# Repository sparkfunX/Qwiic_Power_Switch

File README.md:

# Qwiic Power Switch

A power switch for your Qwiic system.

[Qwiic Power Switch (SPX-16740)](https://www.sparkfun.com/products/16740)

The Qwiic Power Switch is a simple little board which can be used to switch the power to your Qwiic
system. Many Qwiic boards draw very little current when not being used, but there are some that draw
significantly more. The power switch allows you to switch the power to those boards, so you can minimize the
current draw and extend your battery life when you need to.

When the Qwiic Power Switch is turned off, the I2C wires are isolated too which prevents the pull-up
resistors from feeding parasitic power to your Qwiic boards. The power switch can also be used to
isolate a 400kHz bus from a 100kHz bus; the slower bus can be disconnected during fast-mode communication
without disabling the power.

The heart of the Qwiic Power Switch is the TI PCA9536 4-Bit I2C I/O Expander. We have broken out GPIO pins
1 and 2 so you can use them as general purpose inputs or outputs.

## Repository Contents

- **/Documents** - Datasheets etc.
- **/Hardware** - Eagle design files
- **LICENSE.md** contains the licence information

## Library

- **[Arduino Library](https://github.com/sparkfun/SparkFun_Qwiic_Power_Switch_Arduino_Library)** - Library for the power switch

## License Information

This product is _**open source**_!

Please review the LICENSE.md file for license information.

If you have any questions or concerns on licensing, please contact technical support on our [SparkFun forums](https://forum.sparkfun.com/viewforum.php?f=123).

Distributed as-is; no warranty is given.

- Your friends at SparkFun.

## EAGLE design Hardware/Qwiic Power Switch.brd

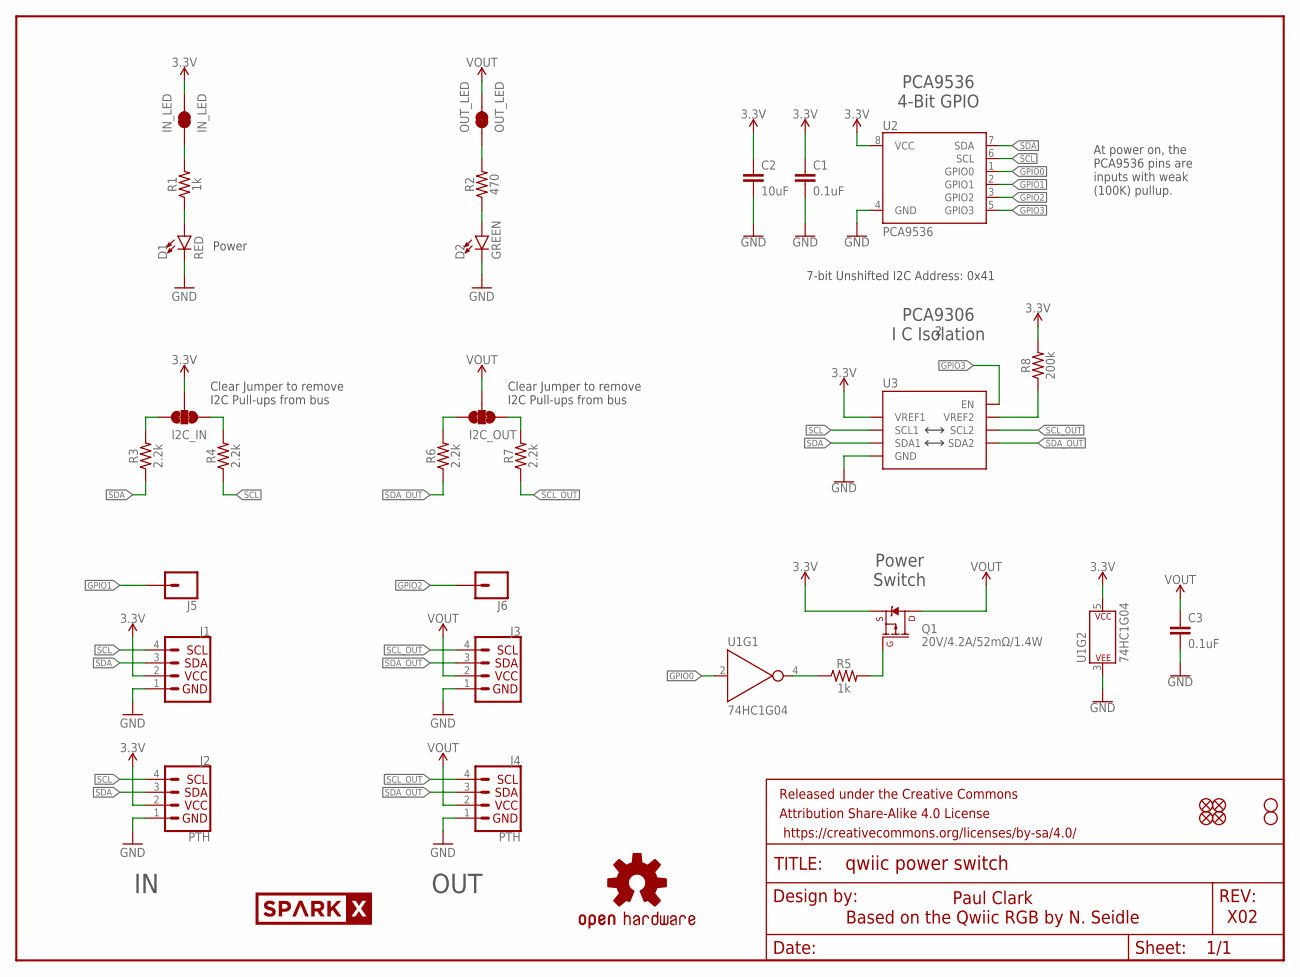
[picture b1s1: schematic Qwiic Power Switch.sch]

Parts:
C1, C3: 0.1uF; 0603
C2: 10uF; 0603
D1: RED; LED-0603
D2: GREEN; LED-0603
FRAME1: FRAME-LETTER; CREATIVE_COMMONS
I2C_IN, I2C_OUT: JUMPER-SMT_3_2-NC_TRACE_SILK; SMT-JUMPER_3_2-NC_TRACE_SILK
IN_LED: IN_LED; SMT-JUMPER_2_NC_TRACE_SILK
J1, J3: Qwiic Right Angle; JST04_1MM_RA
J2, J4: PTH; 1X04_NO_SILK
J5, J6: CONN_01PTH_NO_SILK_YES_STOP; 1X01_NO_SILK
JP1, JP2, JP5, JP6: FIDUCIAL1X2; FIDUCIAL-1X2
JP3, JP4: STAND-OFF
LOGO1: OSHW-LOGOMINI; OSHW-LOGO-MINI
OUT_LED: OUT_LED; SMT-JUMPER_2_NC_TRACE_SILK
Q1: 20V/4.2A/52mΩ/1.4W; SOT23-3
R1, R5: 1k; 0603
R2: 470; 0603
R3, R4, R6, R7: 2.2k; 0603
R8: 200k; 0603
U1: 74HC1G04; SOT353
U2: PCA9536; MSOP8
U3: PCA9306VSSOP_8PIN; VSSOP_8PIN
U$2: SPARKX-LOGO4; SPARKX-MEDIUM

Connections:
3.3V: C1.1, C2.1, I2C_IN.2, IN_LED.2, J1.2, J2.2, Q1.2 (S), R8.2, U1.5 (P$V+), U2.8 (VCC), U3.P2 (VREF1)
GND: C1.2, C2.2, C3.2, D1.C, D2.C, J1.1, J2.1, J3.1, J4.1, U1.3 (P$V-), U2.4 (GND), U3.P1 (GND)
GPIO0: U1.2 (A), U2.1 (GPIO0)
GPIO1: J5.1, U2.2 (GPIO1)
GPIO2: J6.1, U2.3 (GPIO2)
GPIO3: U2.5 (GPIO3), U3.P8 (EN)
unnamed: I2C_IN.1, R4.2
unnamed: I2C_IN.3, R3.2
unnamed: D1.A, R1.1
unnamed: IN_LED.1, R1.2
unnamed: R5.1, U1.4 (Y)
unnamed: Q1.1 (G), R5.2
unnamed: OUT_LED.1, R2.2
unnamed: I2C_OUT.1, R7.2
unnamed: D2.A, R2.1
unnamed: I2C_OUT.3, R6.2
unnamed: R8.1, U3.P7 (VREF2)
SCL: J1.4, J2.4, R4.1, U2.6 (SCL), U3.P3 (SCL1)
SCL_OUT: J3.4, J4.4, R7.1, U3.P6 (SCL2)
SDA: J1.3, J2.3, R3.1, U2.7 (SDA), U3.P4 (SDA1)
SDA_OUT: J3.3, J4.3, R6.1, U3.P5 (SDA2)
VOUT: C3.1, I2C_OUT.2, J3.2, J4.2, OUT_LED.2, Q1.3 (D)

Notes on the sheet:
Paul Clark Based on the Qwiic RGB by N. Seidle
X02
Clear Jumper to remove I2C Pull-ups from bus
Power
7-bit Unshifted I2C Address: 0x41
OUT
At power on, the PCA9536 pins are inputs with weak (100K) pullup.
PCA9536 4-Bit GPIO
PCA9306 I C Isolation
Power Switch

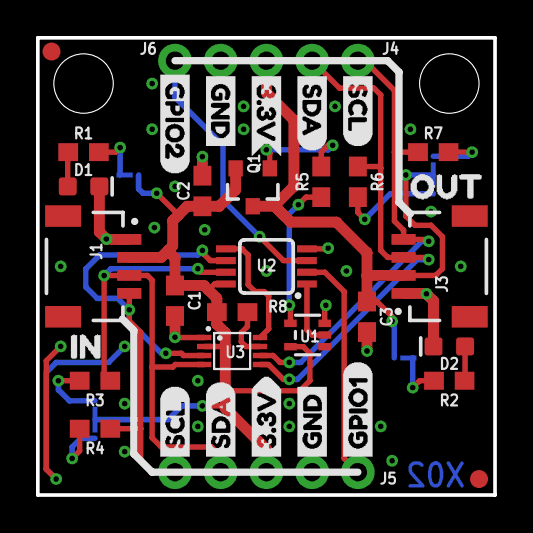
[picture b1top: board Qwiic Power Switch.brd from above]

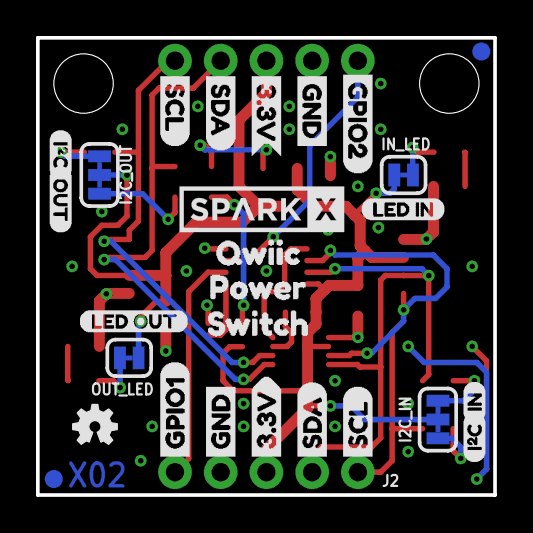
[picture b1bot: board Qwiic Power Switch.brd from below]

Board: 2 copper layers, 25.4 x 25.4 mm, 67 parts (28 on the bottom side), 22 nets.

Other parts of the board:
U$1, U$28: IN0
U$3, U$8, U$13, U$22: GND1
U$4, U$7, U$12, U$23: 3#3V0
U$5, U$11, U$15, U$27: SDA8
U$6, U$9, U$17, U$26: SCL9
U$10, U$18: I_SUPER2_C-()-03
U$14, U$31: OUT0
U$16, U$24: GPIO10
U$19: QWIIC0
U$20, U$25: GPIO20
U$29: LED_IN0
U$30: LED_OUT0
U$32: POWER0
U$34: SWITCH0

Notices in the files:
parts and their libraries:
SparkFun-Resistors: Licensing: Creative Commons ShareAlike 4.0 International - https://creativecommons.org/licenses/by-sa/4.0
SparkFun-Aesthetics: Released under the Creative Commons Attribution Share-Alike 4.0 License
SparkFun-Aesthetics: https://creativecommons.org/licenses/by-sa/4.0
